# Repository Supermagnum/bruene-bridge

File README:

SWR AND POWER MODIFIED BRUENE BRIDGE.

Circuit originally designed by F1FRV . 
This design is applicable for small or high powers, from 100 kHz (or less) to 50 Mhz, from miliwatts to kilowatts, depending on the selected components. For best results, for WIDEBAND use the ferrite "43" material. Materials "4C6 or 4C65" generaly painted in purple, are identical to material "61" and can also be used (with much more turns than "43" for same inductance).

With good electrical and mechanical design, using parts described here, and PCB designed for, 1.8 to 30 (50) MHz directivity can be better than 35 dB, and accuracy in power measurements in the range 1 to 2 %. 

Generaly, if it dont works, it is with people more clever, and better technicians than me, who dont want to follow EXACTLY what is written, and do what they feel instead.

Coaxial line shield must be grounded ONLY 1 side of toroid, 1 time at input connector, and 1 time just near toroid. Place the WIDE ground return strip(s), not a single wire, between coaxial line, circuit board and main ground frame, as close as possible to the toroid, to have the best accuracy in POWER measurements over a wide range of frequencies. For SWR measurements ONLY, this is not very important, as the ratio FWD/REF is independant of absolute values of detected voltages.To avoid parasitic capacitances, place the PCB at least 10 mm above metallic enclosures.

To have perfect balance of the bridge, with the calculated values given by EXCEL sheet, it is important to know the " TRUE " values of the coil(s), resistor R2, and capacitor C1. To know what is the exact Al value of your toroid, coil 5 turns of wire into it, measure with a LC meter, and divide value by 25. With an Ohmmeter, adjust VR1 to the value given by excel sheet.The variable C2 capacitor, as shown, is MANDATORY, to compensate for all tolerances in components values, parasitics. During tests, dont hesitate to modify calculated value of C2 (fixed + adjustable value) to obtain the best balance.Tolerances and parasitic capacitances management are unfortunately not exact sciences. Adjustment of phase compensation C2 must be made, ONLY at bridge maximum frequency of use. If null is not OK with C2, readjust slightly VR1 and C2, at max frequency of use, to obtain perfect null. Reverse bridge in /out to check null symetry.

Check of coil(s) and capacitor C1 exact values can be made with a LC meter, like the one described in pages " Technical " and proposed by DF1SR (ex DD0SB).

Adapt cross sectional area of wires in toroid to maximum current in R2, do not undersize, 3 Amps by square milimeter is a maximum.

Load on detector diodes is a first order parametre for rectified voltages output. Do not hesitate to use operational amplifiers LM358 or LM324 as buffers (they include GND in common mode range). In this case, with very high impedance detectors load, to avoid too high time constant in SWR readings, reduce, if necessary, the values of decoupling capacitors (ceramic) in FWD & REF outputs. 2.2 to 10 nF is OK with operational amplifiers, 100 nF or more without operational amplifiers.

Source for text : F1FRV 's page :
http://f1frv.free.fr/main3h_SWR_Bridges.html

What I have done:
Made a PCB that uses more modern components , as a example is C2 variable cap.
That one is impossible to use for a PCB design because the factory drawings is completely unreadable!
So, I have made adjustments with a smaller adjustable one that goes from 5.5-65pF in paralell with a 100 pF one. So the range of adjustment is 105 to 165 pF.

C1 is a 1pF ±0.5pF 4000V (4kV) Ceramic disc capacitator, clouse enough to the calulated 0,96 pF

I have added solder connectors to SO-239 connectors, 
they will fit if they are soldered in a 45 degree angle as then two of the mounting screws and the center pin can be soldered directly to the board.
It includes voltage dividers so the rectified forward and reverse voltages is suitable for a Aurdinos ADC ports ( 5v DC max ). 
The traces that carries RF is 3mm wide, and short.
It also includes a big area for soldering the coax cable shield to, 
and a copper strap can also be used to squeeze the coax cable shield between the strap and PCB.
It is also possible to mount grounding straps to the PCB. 

R2 is a 30W Through Hole Resistor TO-220-2, in a suitable location for mounting to the sheilded box wall or a heat sink. 

The PFD file contains calculations for up to 2500 W, more than enough because the legal limit in many places is 1000 W.
https://github.com/Supermagnum/bruene-bridge/blob/master/SWR-bridge.pdf

All components is THT.

PCB's:
https://aisler.net/p/KSGINYGY

PCB picture:
https://github.com/Supermagnum/bruene-bridge/blob/master/SWR%20bridge-rendering.jpg

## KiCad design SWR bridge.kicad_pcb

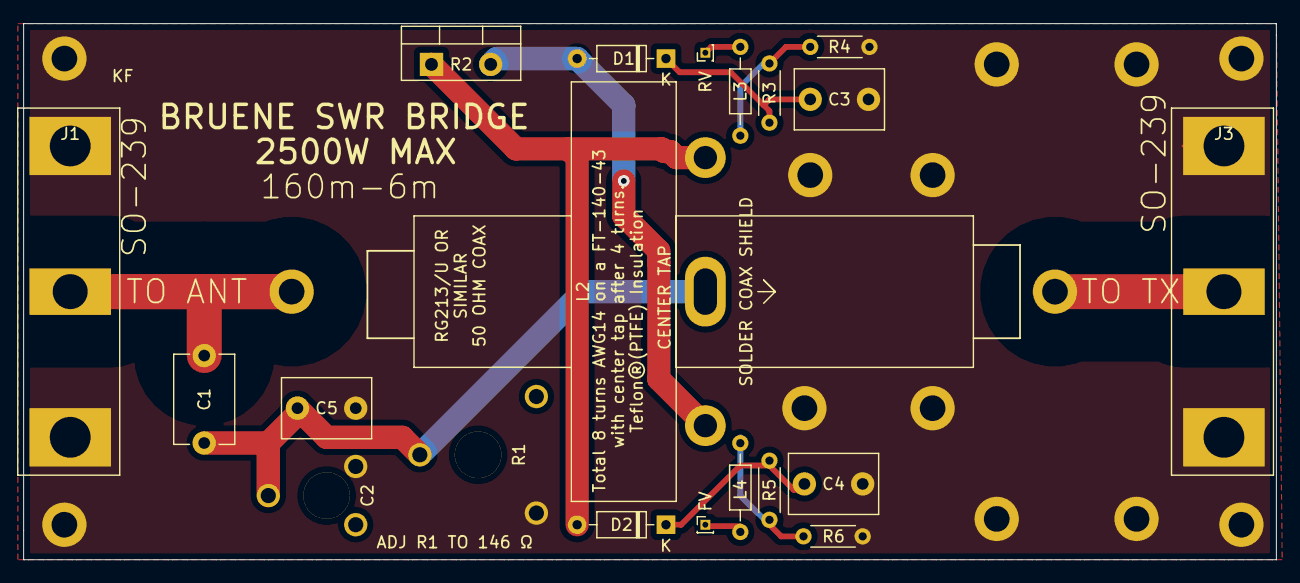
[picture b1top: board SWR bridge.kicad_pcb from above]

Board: 2 copper layers, 107.5 x 46.0 mm, 34 parts (0 on the bottom side), 12 nets.

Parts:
C1: 0.96 pF; C_Disc_D7.5mm_W5.0mm_P7.50mm
C2: 50pF; BC2772-ND
C3, C4: 1nF; C_Disc_D7.5mm_W5.0mm_P5.00mm
C5: 100pF; C_Disc_D7.5mm_W5.0mm_P5.00mm
D1: 1N5711; D_DO-35_SOD27_P7.62mm_Horizontal
D2: 1N4148; D_DO-35_SOD27_P7.62mm_Horizontal
J1, J3: Conn_Coaxial; SO-239-V
J2, J6: Conn_01x01_Female; PinHeader_1x01_P1.00mm_Vertical
J4, J5: Conn_01x01_Female; MountingHole_2.2mm_M2_DIN965_Pad
J7, J8, J9, J10, J12, J13, J14, J15, J16, J17, J18, J19: Conn_01x01_Male; MountingHole_2.2mm_M2_DIN965_Pad
L2: INDUCTOR-TAP
L3, L4: 100uH; R_Axial_DIN0204_L3.6mm_D1.6mm_P7.62mm_Horizontal
R1: 146,025; PT10LV10
R2: 5; TO-220-2_Vertical
R3, R5: 1,5K; R_Axial_DIN0204_L3.6mm_D1.6mm_P5.08mm_Horizontal
R4, R6: 1K; R_Axial_DIN0204_L3.6mm_D1.6mm_P5.08mm_Horizontal

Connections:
/FORWARD: C4.1, D2.1, R5.1
/REF: C3.1, D1.1, R3.1
/RF-IN: J3.1, J5.1
/RF-OUT: C1.1, J1.1, J4.1
/T1: D1.2, L2.2, R2.2
/T2: D2.2, L2.3, R2.1
/T-center: C1.2, C2.1, C5.1, L2.1, R1.1
/VFOR: L4.2, R5.2, R6.1
/vREF: L3.1, R3.2, R4.1
Earth: C2.2, C3.2, C4.2, C5.2, J1.2, J1.3, J3.2, J3.3, J7.1, J8.1, J9.1, J10.1, J12.1, J13.1, J14.1, J15.1, J16.1, J17.1, J18.1, J19.1, R1.2, R4.2, R6.2
unnamed: J2.1, L3.2
unnamed: J6.1, L4.1

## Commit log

2020-09-28 Add files via upload
    added some files.
2020-09-28 Add files via upload
    Added gerber files and pdf files for PCB fabrication.
2020-09-30 Add files via upload
    Updated gerber files
2020-09-30 Add files via upload
    updated pdf files
2020-09-30 Update README
    updated.
2020-09-30 Add files via upload
    added mounting holes for ground straps.
2020-09-30 Add files via upload
    updated pfd files with holes for mounting ground straps.
2020-09-30 Add files via upload
    updated rendering
2020-10-01 Add files via upload
    updated files
2020-10-01 Add files via upload
    updated gerbers
2020-10-01 Add files via upload
    updated pdf files for fabrication
2020-10-01 Add files via upload
    update
2020-10-01 Add files via upload
    updated
2020-10-01 Update README
    update
2020-10-01 Add files via upload
    Changed C4 and C3 to 40 nF , to minimize ripple on the rectified voltages.
2026-06-13 Update README to reflect changes in PCB design
    Removed outdated Dropbox link and clarified PCB design improvements.
2026-06-13 Update README with link to SWR-bridge.pdf
    Added link to SWR-bridge.pdf for reference.
